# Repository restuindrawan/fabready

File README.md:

# fabready

Pre-order checks for KiCad PCBs. fabready finds the mistakes that would cost you a board order before you
place it. It runs as a desktop app, a command-line tool and an MCP server for AI agents, all built on one
Rust engine.

<picture>
  <source media="(prefers-color-scheme: dark)" srcset="docs/images/app-dark.png">
  
</picture>

## What it checks

- **Routing:** unrouted nets and footprints with no connections
- **Fab limits:** track width, via and hole sizes, and copper-to-edge clearance, against JLCPCB's limits or a
  conservative "safe" profile
- **Board:** a missing or open outline, board size and mounting holes
- **Components:** parts rated below what the board puts on them, and parts that are more than the job needs
- **Keyboards:** diodes, matrix wiring, controller pins and wireless antennas
- **KiCad DRC and ERC**, merged in when KiCad is installed

Thin tracks, undersized vias and copper under an antenna can be fixed automatically, with a preview, a
backup and undo.

## Quick start

**Desktop app** (macOS):

```bash
cd app && npm install
npx tauri build --bundles app      # fabready.app in target/release/bundle/macos/
```

The first time it opens, a short setup installs KiCad if it's missing and lets you pick your coding agent. Then
open a KiCad project folder, or drop it on the window. No design yet? Start a new board (the app creates the
KiCad project) or try a sample. The app re-checks every time you save in KiCad. You
can view the board layer by layer, edit it Figma-style (move footprints, route tracks, place vias, measure,
undo), and chat with Claude Code, Codex or OpenCode about the board you have open.

<table>
  <tr>
    <td width="50%">
      <picture>
        <source media="(prefers-color-scheme: dark)" srcset="docs/images/setup-dark.png">
        
      </picture>
    </td>
    <td width="50%">
      <picture>
        <source media="(prefers-color-scheme: dark)" srcset="docs/images/welcome-dark.png">
        
      </picture>
    </td>
  </tr>
  <tr>
    <td align="center">First launch: install KiCad and pick your agent</td>
    <td align="center">Start from your design, a new board or a sample</td>
  </tr>
</table>

**Command line:**

```bash
cargo install --path crates/fabready-cli
fabready check path/to/project
```

**AI agents in their own terminal or editor:** add fabready as an MCP server so your agent can check the
board and apply fixes:

```bash
claude mcp add fabready -- fabready mcp
```

Each board's settings (fab profile, limit overrides, power rails, waived findings) live in a
`fabready.json` next to it. Edit them in the app's Settings tab or by hand.

## Docs

- [Desktop app](docs/app.md): layout, layers, editing tools, fixing problems, agent chat, waiving findings, shortcuts
- [Command line and MCP](docs/command-line.md): commands, output files, exit codes, agent setup
- [Configuration](docs/configuration.md): every `fabready.json` setting
- [Parts review](docs/parts.md): how components are rated
- [Keyboard PCBs](docs/keyboards.md): the extra keyboard checks and firmware helpers
- [CONTRIBUTING.md](CONTRIBUTING.md): setting up, adding checks, fixes and parts, and sending changes
- [AGENTS.md](AGENTS.md): for AI agents using fabready or working on its code

## Privacy

fabready runs entirely on your machine and makes no network requests itself. The app's Agent tab starts the
coding agent you pick (Claude Code, Codex or OpenCode). That agent talks to its own AI provider, and on
first use `npx` downloads its adapter from npm. Nothing is sent until you use the chat. If you click **Install**
for KiCad in the app's setup, it runs Homebrew or winget, which download KiCad. fabready only writes:

- `fabready-out/` next to your board: reports, images, and backups made before automatic fixes
- your `.kicad_pcb`, only when you or your agent apply an automatic fix, or you edit the board in the app
- `fabready.json` next to your board, only when you change settings or waive a finding in the app
- `~/.fabready/agent.json`: the name of the last agent that connected over MCP, shown in the app

## Disclaimer

fabready catches common mistakes, but it doesn't replace your fab's DRC, the parts' datasheets, or your
own review. The fab profiles and part ratings are typical values and may be out of date. Always confirm
with your manufacturer before ordering. KiCad, JLCPCB and other names are trademarks of their owners, and
fabready isn't affiliated with them.

## License

[MIT](LICENSE). Third-party components and trademarks are listed in
[`THIRD-PARTY-NOTICES.md`](THIRD-PARTY-NOTICES.md).

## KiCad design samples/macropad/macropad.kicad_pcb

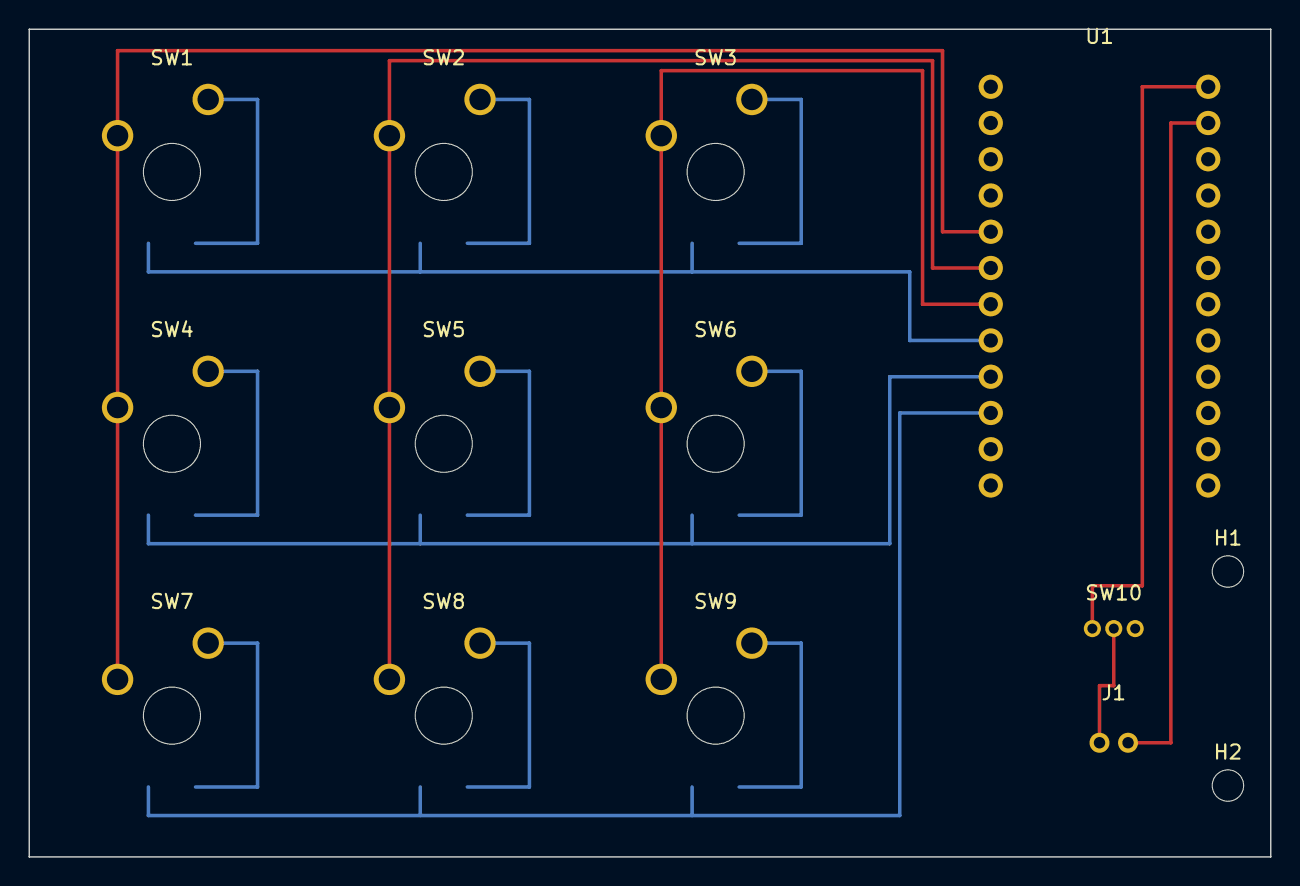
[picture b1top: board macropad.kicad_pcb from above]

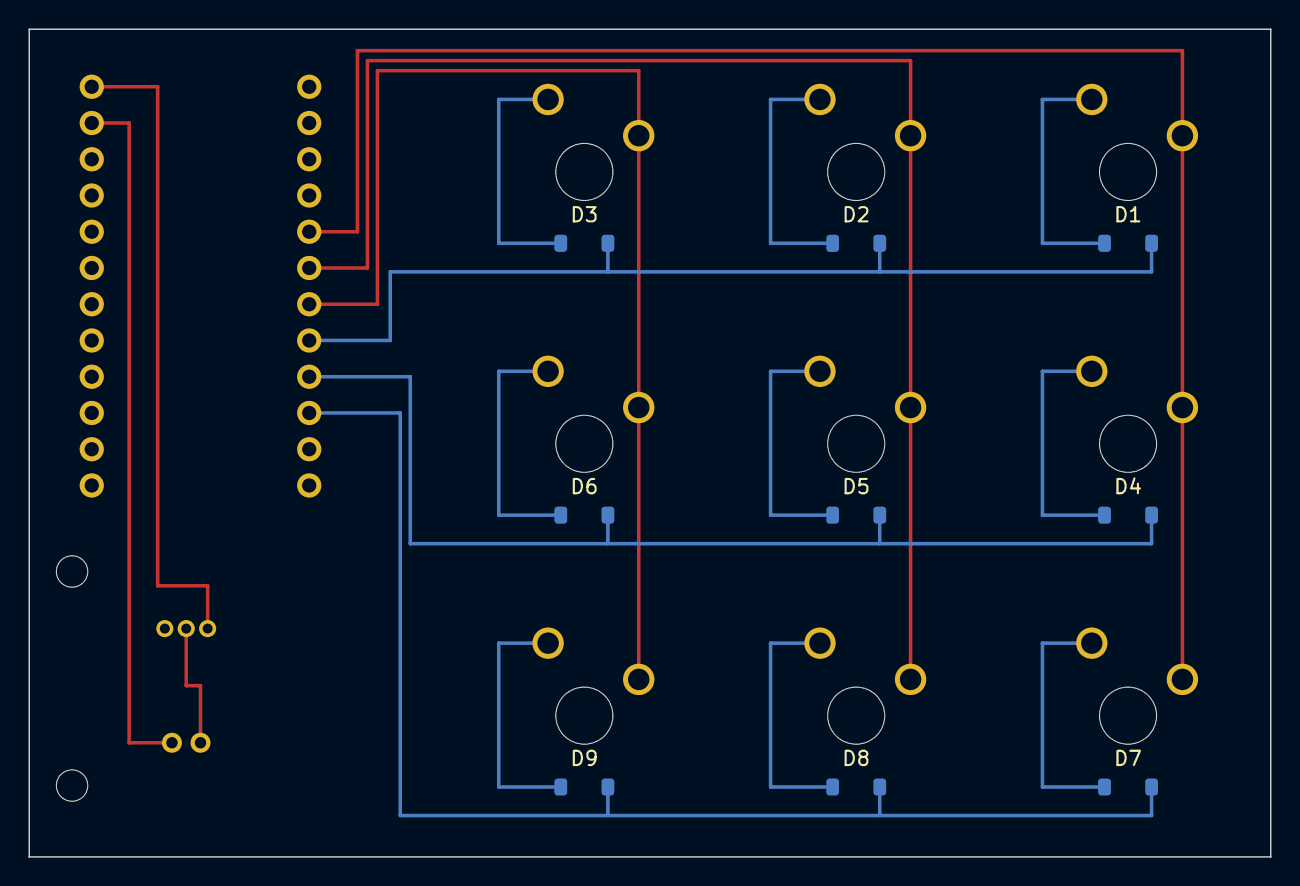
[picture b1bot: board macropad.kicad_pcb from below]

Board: 2 copper layers, 87.0 x 58.0 mm, 23 parts (9 on the bottom side), 18 nets.

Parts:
D1, D2, D3, D4, D5, D6, D7, D8, D9: 1N4148W; D_SOD-123
H1, H2: MountingHole; MountingHole_2.2mm_M2
J1: Battery; JST_PH_2pin
SW1, SW2, SW3, SW4, SW5, SW6, SW7, SW8, SW9: SW_Push; SW_MX_1u
SW10: Power; SW_Slide_SPDT
U1: nice!nano; nice_nano

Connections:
BAT+: J1.1 (+), SW10.2
COL0: SW1.1, SW4.1, SW7.1, U1.5 (D1)
COL1: SW2.1, SW5.1, SW8.1, U1.6 (D0)
COL2: SW3.1, SW6.1, SW9.1, U1.7 (D4)
GND: J1.2 (-), U1.3 (GND), U1.4 (GND), U1.23 (GND)
unnamed: D1.2 (A), SW1.2
unnamed: D2.2 (A), SW2.2
unnamed: D3.2 (A), SW3.2
unnamed: D4.2 (A), SW4.2
unnamed: D5.2 (A), SW5.2
unnamed: D6.2 (A), SW6.2
unnamed: D7.2 (A), SW7.2
unnamed: D8.2 (A), SW8.2
unnamed: D9.2 (A), SW9.2
RAW: SW10.1, U1.24 (RAW)
ROW0: D1.1 (K), D2.1 (K), D3.1 (K), U1.8 (C6)
ROW1: D4.1 (K), D5.1 (K), D6.1 (K), U1.9 (D7)
ROW2: D7.1 (K), D8.1 (K), D9.1 (K), U1.10 (E6)

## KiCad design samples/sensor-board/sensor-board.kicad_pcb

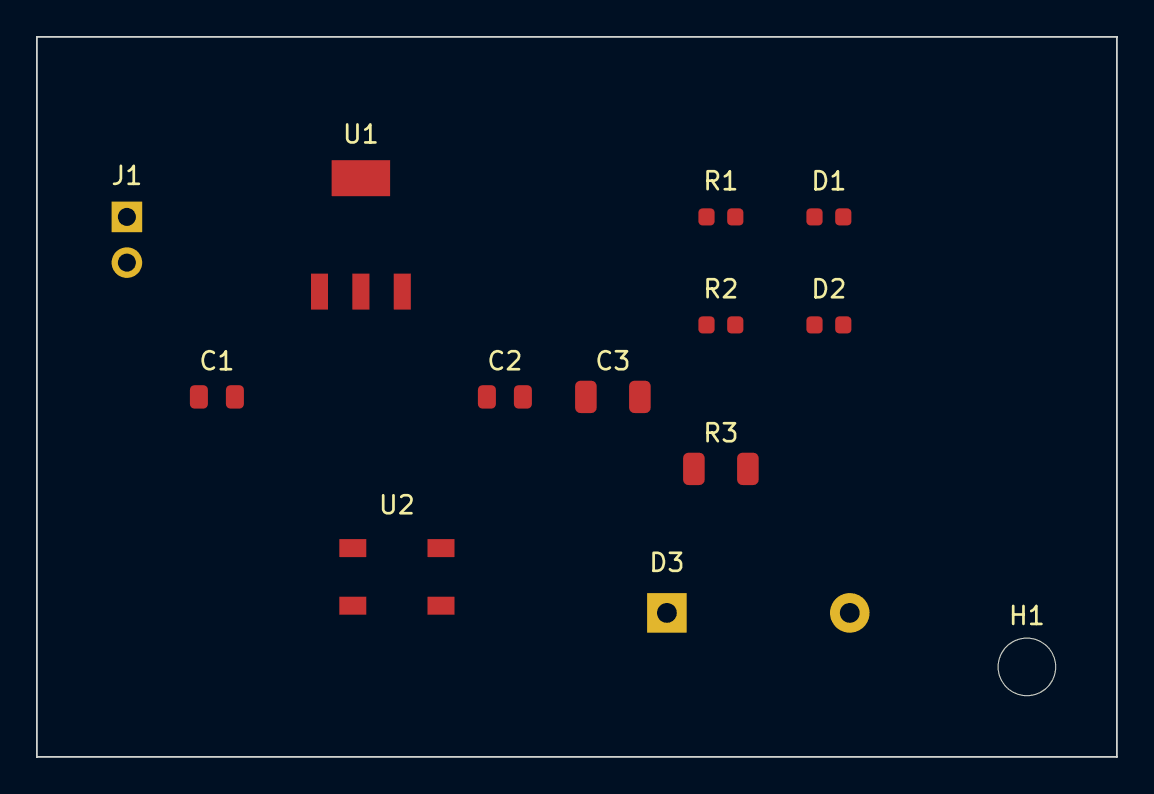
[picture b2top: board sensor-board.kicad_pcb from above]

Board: 2 copper layers, 60.0 x 40.0 mm, 13 parts (0 on the bottom side), 6 nets, no tracks yet.

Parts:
C1: 10uF 6.3V; C_0805_2012Metric
C2: 22uF 10V; C_0805_2012Metric
C3: 100nF 50V; C_1206_3216Metric
D1: RED; LED_0603_1608Metric
D2: BLUE; LED_0603_1608Metric
D3: 1N4007; D_DO-41_SOD81_P10.16mm_Horizontal
H1: MountingHole; MountingHole_3.2mm_M3
J1: Conn_01x02; PinHeader_1x02_P2.54mm_Vertical
R1: 1k; R_0603_1608Metric
R2: 47; R_0603_1608Metric
R3: 10k; R_1206_3216Metric
U1: AMS1117-3.3; SOT-223-3_TabPin2
U2: WS2812B; LED_WS2812B_PLCC4_5.0x5.0mm_P3.2mm

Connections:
+3V3: C2.1, C3.1, R1.1, R3.1, U1.2 (VO), U2.1 (VDD)
GND: C1.2, C2.2, C3.2, D1.1 (K), D2.1 (K), J1.2, U1.1 (GND), U2.3 (VSS)
unnamed: D1.2 (A), R1.2
unnamed: D2.2 (A), R2.2
SDA: D3.1 (K), R3.2
VBUS: C1.1, J1.1, R2.1, U1.3 (VI)
